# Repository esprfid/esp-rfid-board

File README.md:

# ESP12 / ESP12F / ESP12E / ESP12S Wiegand rfid board

Small ESP12F breakout board, custom built for Wiegand RFID readers.

### You can get this board from my Tindie shop:

WARNING: Although it’s rated for more than 12V, i strongly suggest to use maximum of 12V input!

Check the image for explanation of how to hook up the reader

&nbsp;&nbsp;

** There is a resistor on the way from ESP to buzzer due to strange behaviour of busser that ditn't react to HIGN/LOW except if there is a resitor on the way from ESP to Wiegand reader.

Custom pads

&nbsp;&nbsp;
<br>
** New board has marked pads

**Option 1:**
Solder 2 and 1 on both pads results in passing “Ring” tactile switch/button to ESP8266 pin GPIO14

**Option 2:**
Solder 3 and 2 on both pads results in passing “Ring” switch to a terminal on  another side of board.

**Option 3:**
Solder 1 and 3 on both pads results in passing terminal pins to ESP8266 GPIO14, planned so that you can hook door status magnet sensor. In this case, you can’t use “Ring” button in Option 1. or 2.

&nbsp;&nbsp;

&nbsp;&nbsp;
&nbsp;&nbsp;
&nbsp;&nbsp;

* BOM has some mistakes, contact me if you need some help.

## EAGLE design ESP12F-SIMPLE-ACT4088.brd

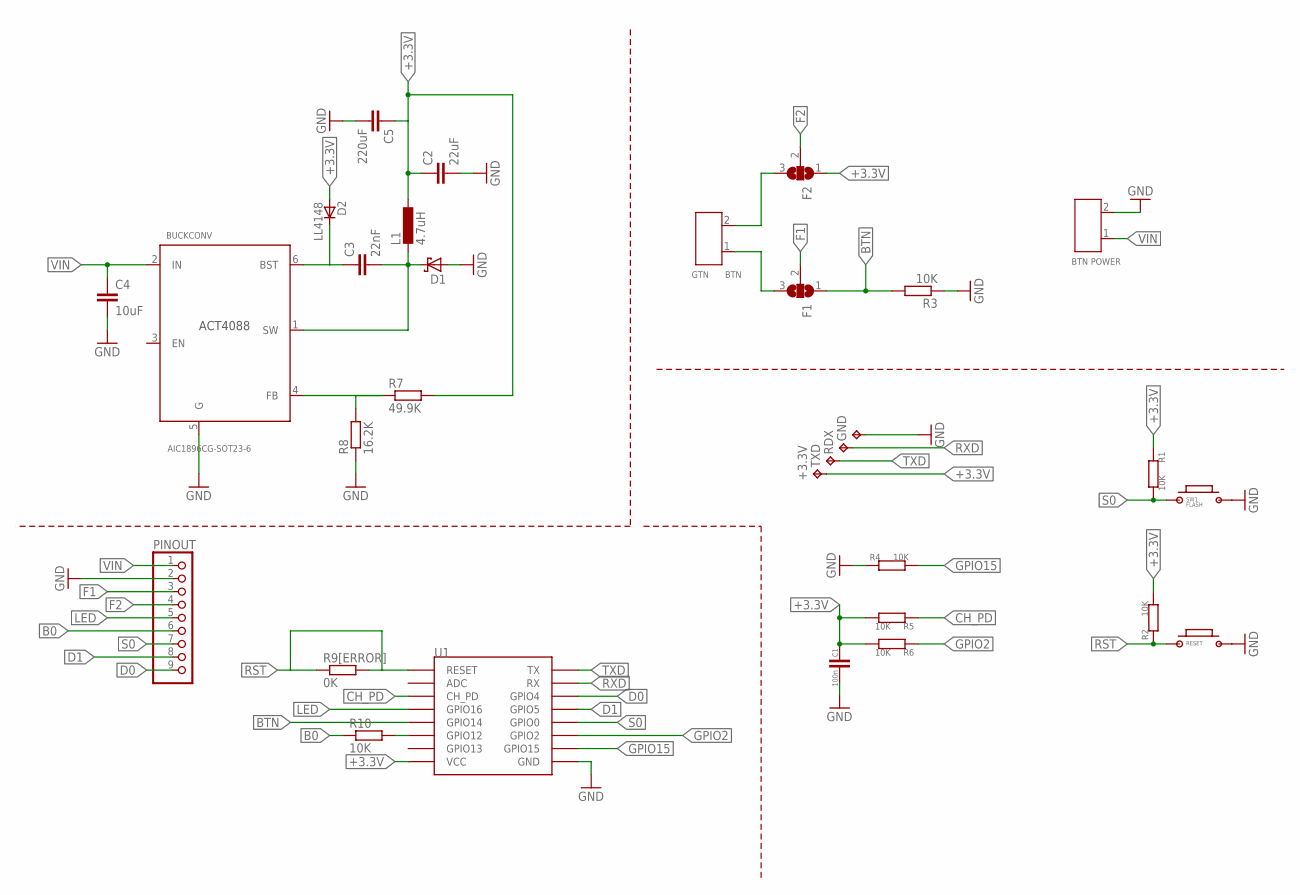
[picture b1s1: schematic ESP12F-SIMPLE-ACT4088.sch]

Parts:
+3.3V: TPTP15R; TP15R
BTN: GTN; H2-3.5-7.0X7.0MM
BUCKCONV: AIC1896CG-SOT23-6; SOT-23-6
C1: 100n; C_0805
C2: 22uF; C0805K
C3: 22nF; C0805K
C4: 10uF; C0805K
C5: 220uF; C1210
D1: SCHOTTKY-DIODESMD; SMB
D2: LL4148; SOD80_DO213AA_MINIMELF
F1, F2: SJ2WX; SJ_2XX
GND: TPTP15R; TP15R
L1: 4.7uH; L3225M
PINOUT: PINHD-1X9; 1X09
POWER: BTN; H2-3.5-7.0X7.0MM
R1, R2, R4, R5, R6: 10K; R_0805
R3, R10: 10K; R0805
R7: 49.9K; R0805
R8: 16.2K; R0805
R9[ERROR]: 0K; R0805
RDX: TPTP15R; TP15R
RESET: BUTTON-2PSWITCH-TURTLE-2P; 2P-SWITCH-TURTLE
SW1: FLASH; 2P-SWITCH-TURTLE
TXD: TPTP15R; TP15R
U1: ESP12SMD; ESP12-SMD

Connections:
+3.3V: +3.3V.TP, C1.1, C2.1, C5.1, D2.A, F2.1, L1.1, R1.1, R2.2, R5.2, R6.2, R7.2, U1.VCC
B0: PINOUT.6, R10.1
BTN: F1.1, R3.2, U1.GPIO14
CH_PD: R5.1, U1.CH_PD
D0: PINOUT.9, U1.GPIO4
D1: PINOUT.8, U1.GPIO5
F1: F1.2, PINOUT.3
F2: F2.2, PINOUT.4
GND: BUCKCONV.5 (G), C1.2, C2.2, C4.2, C5.2, D1.A, GND.TP, PINOUT.2, POWER.2, R3.1, R4.1, R8.1, RESET.2, SW1.2, U1.GND
GPIO2: R6.1, U1.GPIO2
GPIO15: R4.2, U1.GPIO15
LED: PINOUT.5, U1.GPIO16
unnamed: BUCKCONV.1 (SW), C3.2, D1.C, L1.2
unnamed: R10.2, U1.GPIO12
unnamed: BUCKCONV.6 (BST), C3.1, D2.C
unnamed: BUCKCONV.4 (FB), R7.1, R8.2
unnamed: BTN.1, F1.3
unnamed: BTN.2, F2.3
RST: R2.1, R9[ERROR].1, R9[ERROR].2, RESET.1, U1.RESET
RXD: RDX.TP, U1.RXD0 (RX)
S0: PINOUT.7, R1.2, SW1.1, U1.GPIO0
TXD: TXD.TP, U1.TXD0 (TX)
VIN: BUCKCONV.2 (IN), C4.1, PINOUT.1, POWER.1

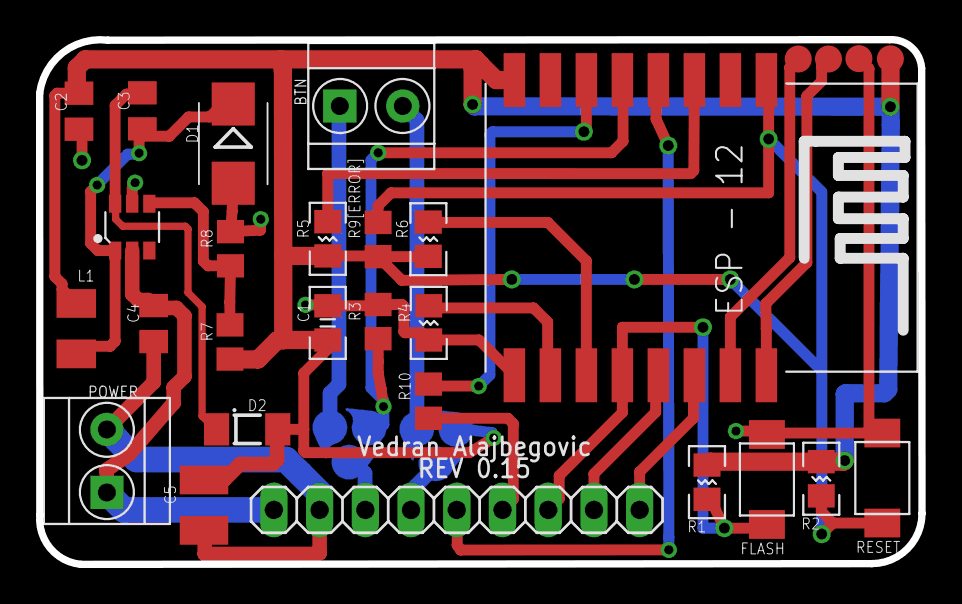
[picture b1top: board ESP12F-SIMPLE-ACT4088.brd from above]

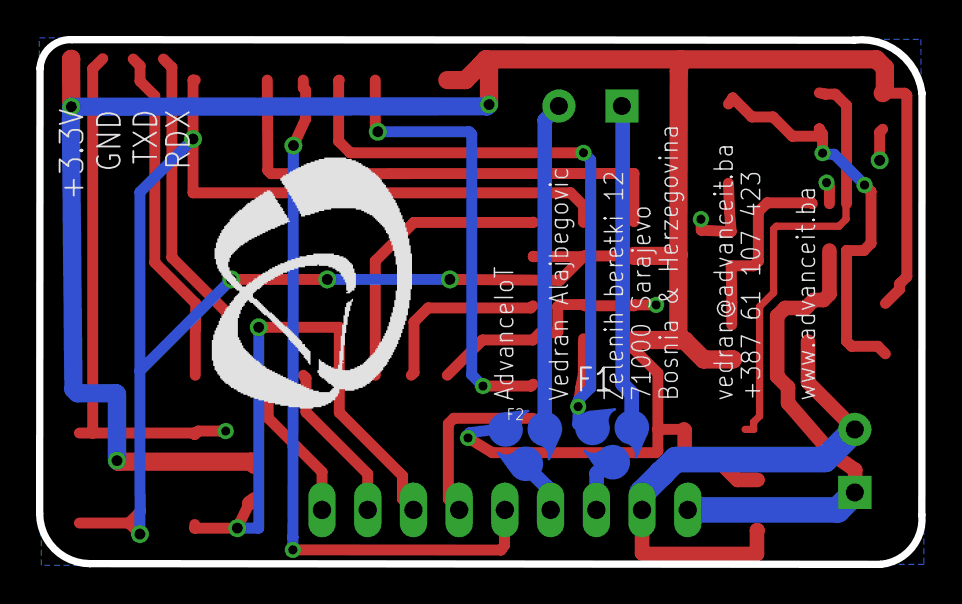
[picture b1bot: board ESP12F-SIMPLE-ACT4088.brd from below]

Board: 2 copper layers, 49.0 x 29.1 mm, 31 parts (2 on the bottom side), 23 nets.

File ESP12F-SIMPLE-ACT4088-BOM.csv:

Part,Value,Device,Package,Description
BTN,GTN,SCREW-TERMINAL-GREEN(2P-3.5),H2-3.5-7.0X7.0MM,320110028
BUCKCONV,AIC1896CG-SOT23-6,ACT4088-(SOT23-6),SOT-23-6,310030104
C1,100n,CAPC0805,C_0805,
C2,22uF,C-EUC0805K,C0805K,"CAPACITOR, European symbol"
C3,22nF,C-EUC0805K,C0805K,"CAPACITOR, European symbol"
C4,10uF,C-EUC0805K,C0805K,"CAPACITOR, European symbol"
C5,220uF,CAPC1411,1411/3528,CAPACITOR 6.3V/220UF
D1,,SCHOTTKY-DIODESMD,SMB,Schottky Diode
D2,LL4148,LL4148,SOD80_DO213AA_MINIMELF,1N4148 General Purpose Rectifie
F1,,SJ2W,SJ_2,SMD solder JUMPER
F2,,SJ2W,SJ_2,SMD solder JUMPER
L1,4.7uH,L-EUL3225M,L3225M,"INDUCTOR, European symbol"
PINOUT,,PINHD-1X9,1X09,PIN HEADER
POWER,BTN,SCREW-TERMINAL-GREEN(2P-3.5),H2-3.5-7.0X7.0MM,320110028
R1,10K,RESISTORR0805,R_0805,
R2,10K,RESISTORR0805,R_0805,
R3,10K,R-EU_R0805,R0805,"RESISTOR, European symbol"
R4,10K,RESISTORR0805,R_0805,
R5,10K,RESISTORR0805,R_0805,
R6,10K,RESISTORR0805,R_0805,
R7,49.9K,R-EU_R0805,R0805,"RESISTOR, European symbol"
R8,16.2K,R-EU_R0805,R0805,"RESISTOR, European symbol"
R9,10K,R-EU_R0805,R0805,"RESISTOR, European symbol"
R10,10K,R-EU_R0805,R0805,"RESISTOR, European symbol"
RESET,,BUTTON-2PSWITCH-TURTLE-2P,2P-SWITCH-TURTLE,
SW1,FLASH,BUTTON-2PSWITCH-TURTLE-2P,2P-SWITCH-TURTLE,
TP1,TPTP15R,TPTP15R,TP15R,Test pad
TP2,TPTP15R,TPTP15R,TP15R,Test pad
TP3,TPTP15R,TPTP15R,TP15R,Test pad
TP4,TPTP15R,TPTP15R,TP15R,Test pad
U1,,ESP12SMD,ESP12-SMD,ESP8266 Wifi module 12

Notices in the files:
parts and their libraries:
SparkFun-Aesthetics: Licensing: Creative Commons ShareAlike 4.0 International - https://creativecommons.org/licenses/by-sa/4.0
